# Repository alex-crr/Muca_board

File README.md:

# MUCA board v2 (MUCA2)

Readout board for printed stretchable mutual-capacitance skin sensors (reSkin / Skin-On), redesigned from the [MUCA](https://muca.cc/) board.

Status: rev 0.1, schematic complete (ERC clean), board routed (DRC 0 errors, silkscreen warnings only). Not fabricated.

## Architecture

| Block | Part | Notes |
|---|---|---|
| Touch AFE | FocalTech FT5316DME (QFN-48) | 21 TX x 12 RX = 252 nodes, I2C 0x38, <= 400 kHz. Same controller family as the original MUCA. |
| Host | Seeed Studio XIAO ESP32S3 (SMD castellated) | USB-C, 3.3 V regulator, RESET/BOOT buttons on the module. TWAI (CAN 2.0B). |
| CAN | SN65HVD230, NUP2105L TVS | 2x JST-GH 4-pin, DroneCAN pinout (1 +5 V, 2 CANH, 3 CANL, 4 GND). Solder-jumper 120 ohm termination. |
| Power | LM66100 ideal diode CAN 5 V -> XIAO 5V pin | USB powers the board through the XIAO; CAN 5 V back-feeds through the diode. XIAO 3V3 powers the whole board; ferrite-filtered +3.3VA for the FT5316 analog supplies. Max input 5.5 V. |
| Sensor I/O | 2x 2.54 mm right-angle female socket, 1x10 | J3: TX1-TX10, J4: RX1-RX10 (10 x 10), pin 1 at the right end. Sensor tails carry Amphenol Clincher 66226 pin connectors (e.g. 66226-037LF, 5 pos) on pins 1-5. |
| Debug | 7 LEDs, 7 test points | LEDs, labelled on silkscreen: CAN PWR, 3V3, TOUCH PWR (FT5316 analog rail), and the status row FAULT / COMM / SENSE / HEARTBEAT (left to right). Test points on +5V, +3V3, GND and the I2C/INT/RST bus. |

## Layout

70 x 50 mm, 2 layers. Sensing side (sensor sockets + FT5316) on the top edge, digital side (XIAO, CAN, power) on the bottom. TX/RX fans are hand-routed on F.Cu, non-crossing, over a solid B.Cu GND plane (no-tracks keepout under the sensing zone). Only the 4-wire I2C/INT/RST bus crosses between the two halves. The remaining nets were routed with a grid router: signals 0.2 mm, +3V3/+3.3VA/CAN_VBUS 0.3 mm, +5V 0.4 mm. The I2C bus needs 6 vias because J7's pin order is the reverse of U6's. Every GND pad reaches the B.Cu pour through a via.

## XIAO pin map

| XIAO pin | GPIO | Function |
|---|---|---|
| D0 / D1 | GPIO1 / GPIO2 | CAN_TX / CAN_RX |
| D2 | GPIO3 | TP_SCL |
| D3 | GPIO4 | TP_SDA |
| D4 | GPIO5 | TP_INT |
| D5 | GPIO6 | TP_RST (active low, 10 kohm pull-up) |
| D6-D9 | GPIO43, 44, 7, 8 | LED HB / SENSE / COMM / FAULT |
| D10 | GPIO9 | free |

I2C is not on the XIAO default pins: use `Wire.begin(4, 3)` (SDA, SCL). D6/D7 are UART0, so the HB/SENSE LEDs flicker with boot logs on reset.

## Files

- `MUCA2.kicad_pro` - project (hierarchical: Power, MCU, Touch AFE, CAN)
- `MUCA2.kicad_sym` - project symbols (FT5316DME from the FocalTech FT5x16 datasheet, XIAO ESP32S3 from the Seeed library)
- `MUCA2.pretty/` - project footprints (XIAO ESP32S3 SMD)

## Open points

- FT5316DME ships blank: flash `MuCaFirmware.bin` over I2C from the ESP32 ([muca-firmware](https://github.com/muca-board/muca-firmware)).
- FT5316DME sourcing not confirmed.
- Verify socket and JST-GH opening direction in the 3D viewer.
- H2 sits at (166.5, 123), 11 mm below H1, to leave room for the RX1 trace to J4 pin 1: the mounting pattern is not a rectangle.
- Silkscreen cleanup (overlapping references), no mounting holes yet.
- CAN bus power limited to 5 V nominal; a 12-24 V bus needs a buck converter.

Related: [Muca_lib](https://github.com/muca-board/Muca), [Muca_experiences](https://github.com/alex-crr/Muca_experiences).

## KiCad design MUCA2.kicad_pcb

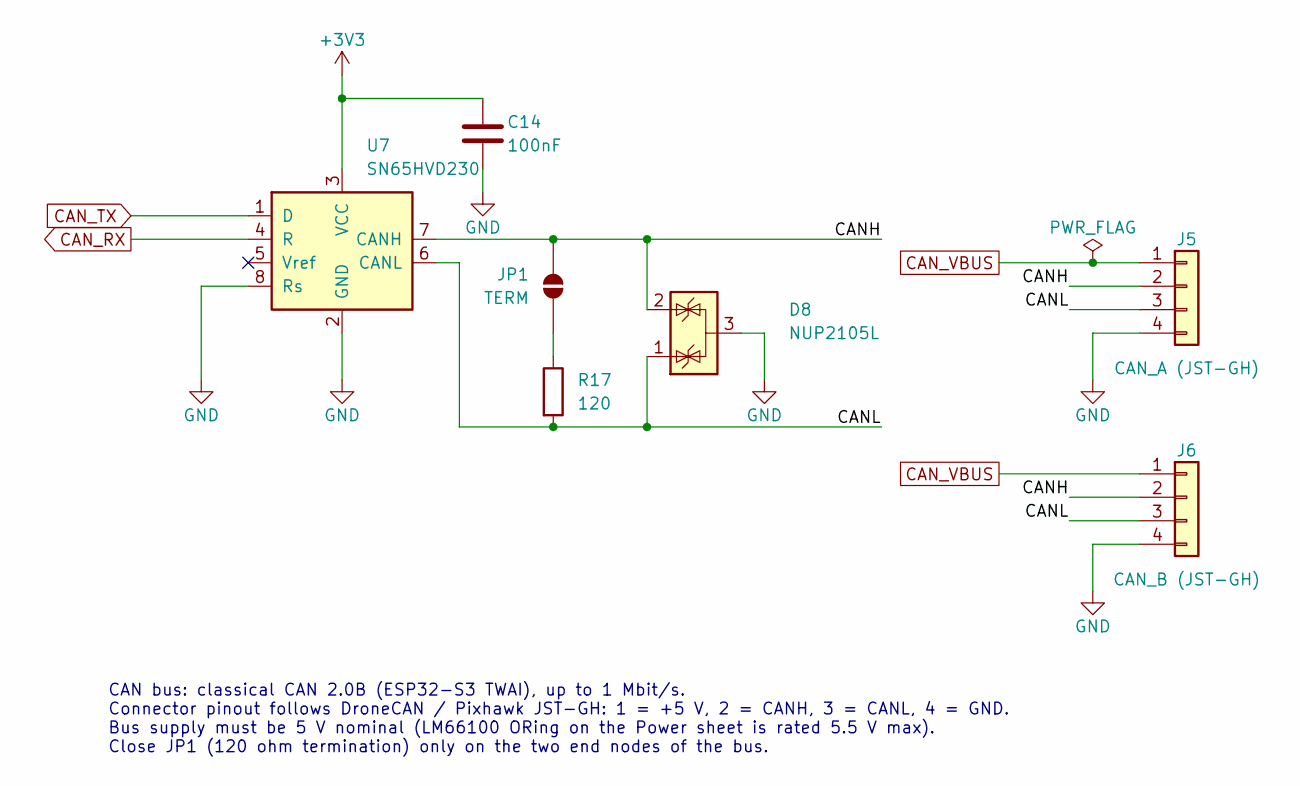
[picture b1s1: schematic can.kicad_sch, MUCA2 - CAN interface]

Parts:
C14: 100nF; C_0402_1005Metric
D8: NUP2105L; SOT-23
J5: CAN_A (JST-GH); JST_GH_SM04B-GHS-TB_1x04-1MP_P1.25mm_Horizontal
J6: CAN_B (JST-GH); JST_GH_SM04B-GHS-TB_1x04-1MP_P1.25mm_Horizontal
JP1: TERM; SolderJumper-2_P1.3mm_Open_RoundedPad1.0x1.5mm
R17: 120; R_0603_1608Metric
U7: SN65HVD230; SOIC-8_3.9x4.9mm_P1.27mm

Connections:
+3V3: C14.1, U7.3 (VCC); also elsewhere on the board
CANH: D8.2 (K), J5.2, J6.2, JP1.2 (B), U7.7 (CANH)
CANL: D8.1 (K), J5.3, J6.3, R17.2, U7.6 (CANL)
CAN_RX: U7.4 (R); also elsewhere on the board
CAN_TX: U7.1 (D); also elsewhere on the board
CAN_VBUS: J5.1, J6.1; also elsewhere on the board
GND: C14.2, D8.3 (A), J5.4, J6.4, U7.2 (GND), U7.8 (Rs); also elsewhere on the board
unnamed: JP1.1 (A), R17.1

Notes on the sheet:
CAN bus: classical CAN 2.0B (ESP32-S3 TWAI), up to 1 Mbit/s. Connector pinout follows DroneCAN / Pixhawk JST-GH: 1 = +5 V, 2 = CANH, 3 = CANL, 4 = GND. Bus supply must be 5 V nominal (LM66100 ORing on the Power sheet is rated 5.5 V max). Close JP1 (120 ohm termination) only on the two end nodes of 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

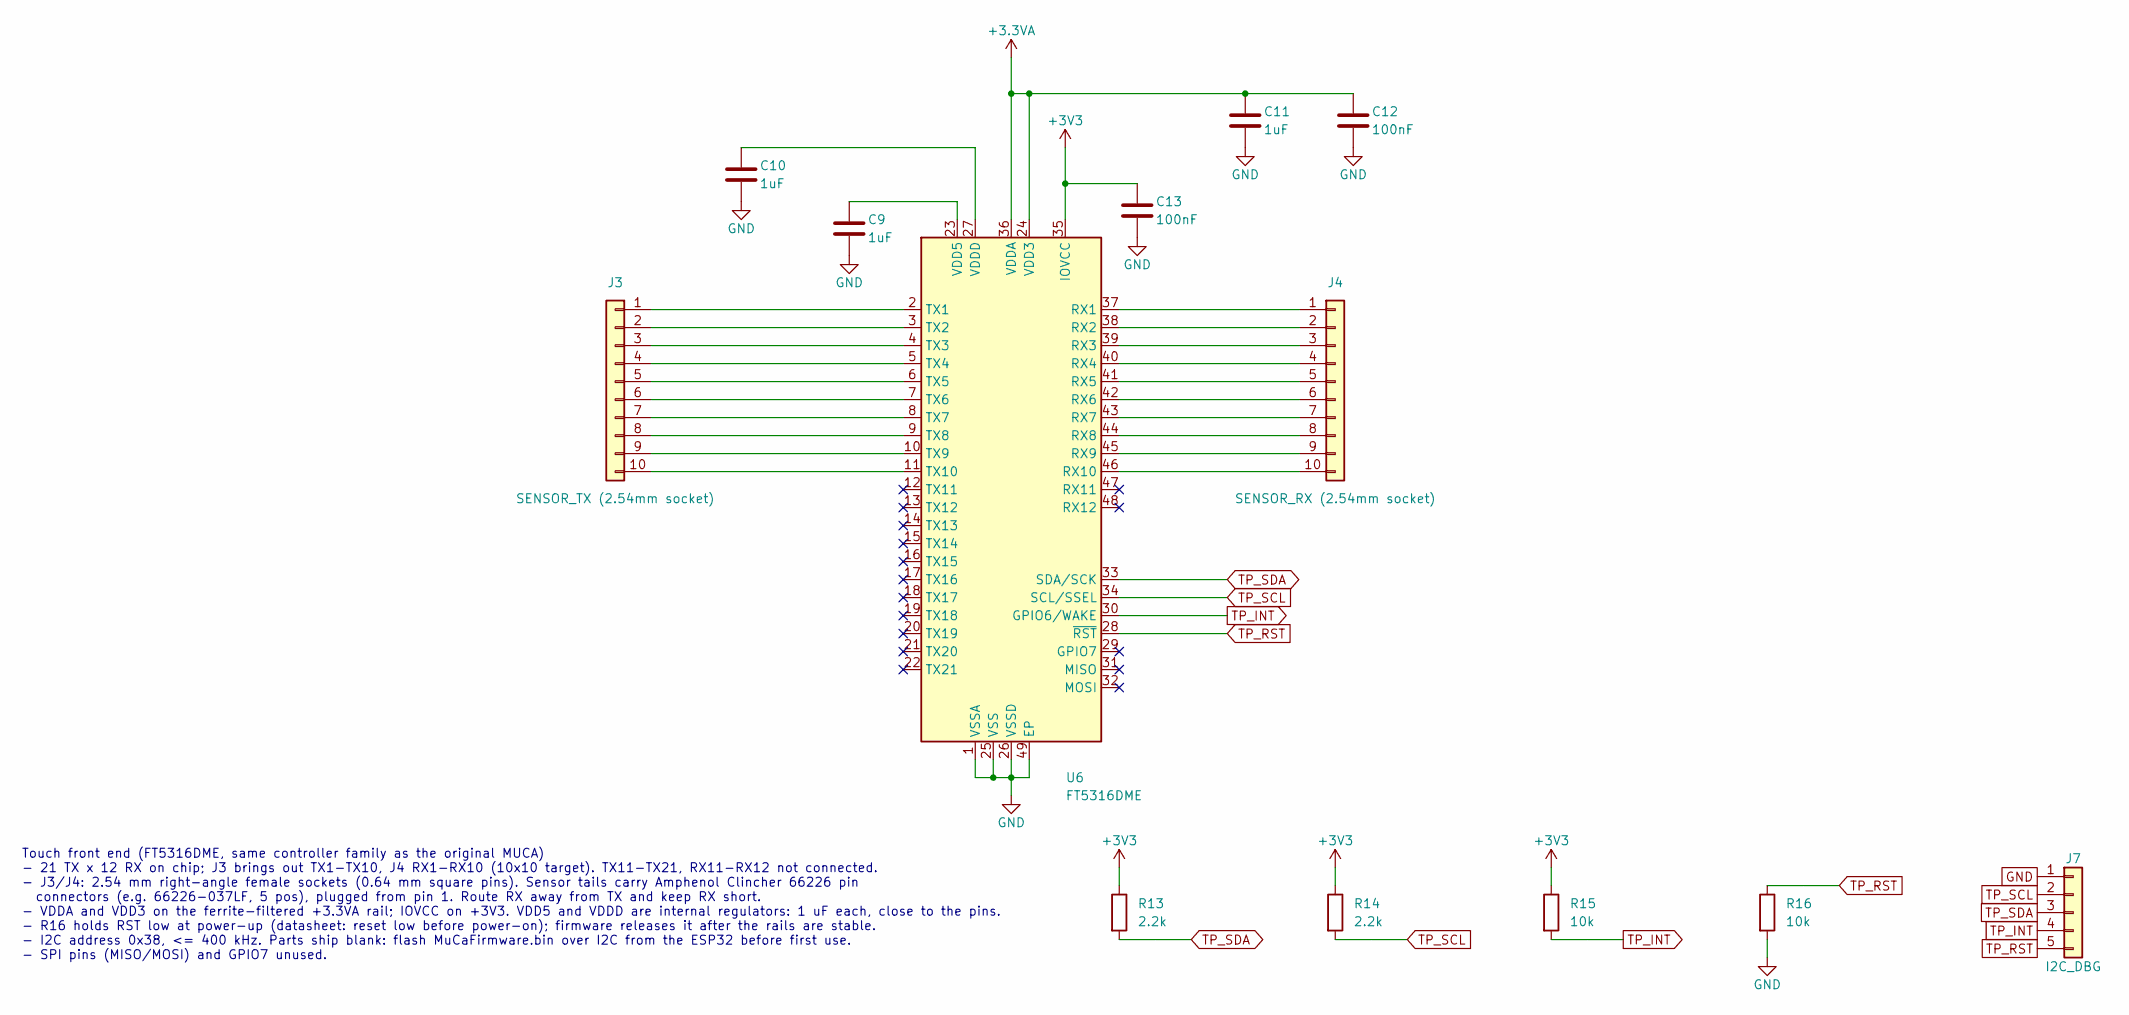
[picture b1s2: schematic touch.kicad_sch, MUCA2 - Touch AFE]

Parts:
C9, C10, C11: 1uF; C_0402_1005Metric
C12, C13: 100nF; C_0402_1005Metric
J3: SENSOR_TX (2.54mm socket); PinSocket_1x10_P2.54mm_Horizontal
J4: SENSOR_RX (2.54mm socket); PinSocket_1x10_P2.54mm_Horizontal
J7: I2C_DBG; PinHeader_1x05_P2.54mm_Vertical
R13, R14: 2.2k; R_0402_1005Metric
R15, R16: 10k; R_0402_1005Metric
U6: FT5316DME; QFN-48-1EP_6x6mm_P0.4mm_EP4.6x4.6mm

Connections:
+3.3VA: C11.1, C12.1, U6.24 (VDD3), U6.36 (VDDA); also elsewhere on the board
+3V3: C13.1, R13.1, R14.1, R15.1, U6.35 (IOVCC); also elsewhere on the board
GND: C9.2, C10.2, C11.2, C12.2, C13.2, J7.1, R16.2, U6.1 (VSSA), U6.25 (VSS), U6.26 (VSSD), U6.49 (EP); also elsewhere on the board
unnamed: C9.1, U6.23 (VDD5)
unnamed: C10.1, U6.27 (VDDD)
unnamed: J3.1, U6.2 (TX1)
unnamed: J3.2, U6.3 (TX2)
unnamed: J3.3, U6.4 (TX3)
unnamed: J3.4, U6.5 (TX4)
unnamed: J3.5, U6.6 (TX5)
unnamed: J3.6, U6.7 (TX6)
unnamed: J3.7, U6.8 (TX7)
unnamed: J3.8, U6.9 (TX8)
unnamed: J3.9, U6.10 (TX9)
unnamed: J3.10, U6.11 (TX10)
unnamed: J4.1, U6.37 (RX1)
unnamed: J4.2, U6.38 (RX2)
unnamed: J4.3, U6.39 (RX3)
unnamed: J4.4, U6.40 (RX4)
unnamed: J4.5, U6.41 (RX5)
unnamed: J4.6, U6.42 (RX6)
unnamed: J4.7, U6.43 (RX7)
unnamed: J4.8, U6.44 (RX8)
unnamed: J4.9, U6.45 (RX9)
unnamed: J4.10, U6.46 (RX10)
TP_INT: J7.4, R15.2, U6.30 (GPIO6/WAKE); also elsewhere on the board
TP_RST: J7.5, R16.1, U6.28 (~RST); also elsewhere on the board
TP_SCL: J7.2, R14.2, U6.34 (SCL/SSEL); also elsewhere on the board
TP_SDA: J7.3, R13.2, U6.33 (SDA/SCK); also elsewhere on the board

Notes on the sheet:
Touch front end (FT5316DME, same controller family as the original MUCA) - 21 TX x 12 RX on chip; J3 brings out TX1-TX10, J4 RX1-RX10 (10x10 target). TX11-TX21, RX11-RX12 not connected. - J3/J4: 2.54 mm right-angle female sockets (0.64 mm square pins). Sensor tails carry Amphenol Clincher 66226 pin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

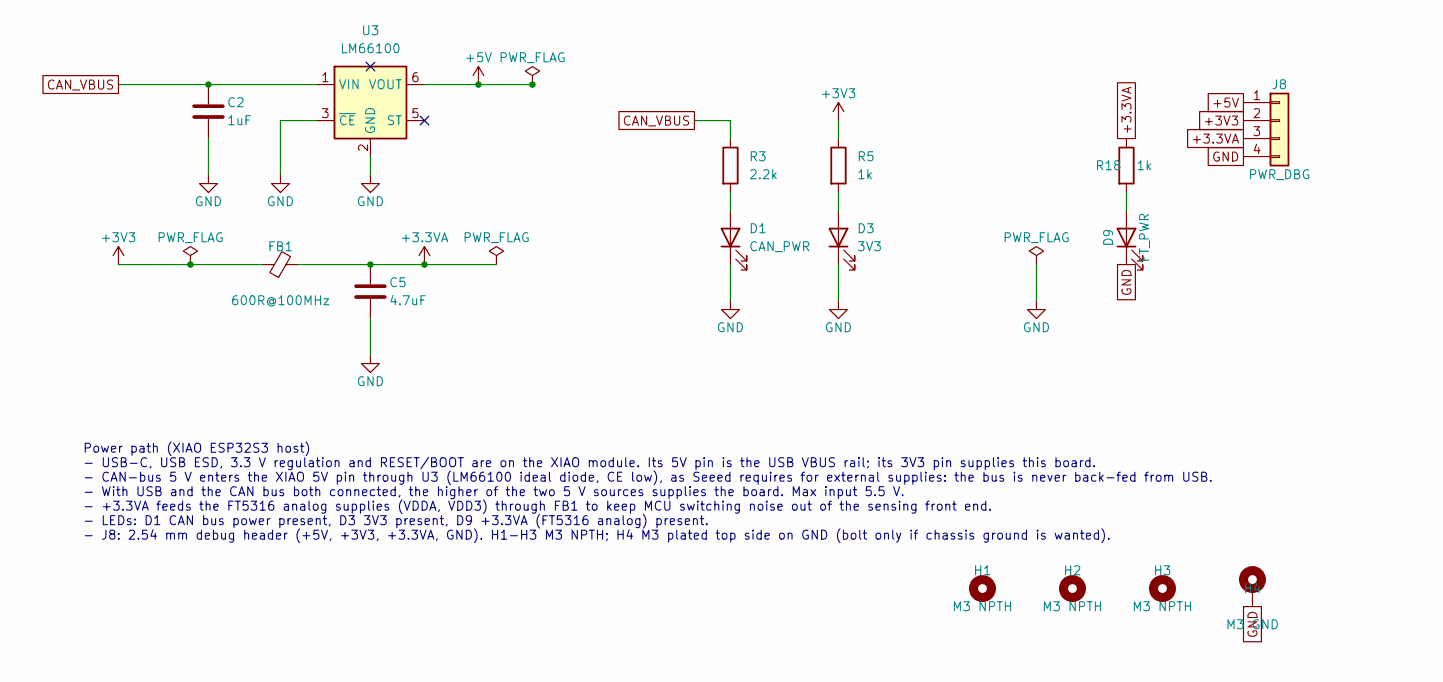
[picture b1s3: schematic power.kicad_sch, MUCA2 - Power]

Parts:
C2: 1uF; C_0402_1005Metric
C5: 4.7uF; C_0603_1608Metric
D1: CAN_PWR; LED_0603_1608Metric
D3: 3V3; LED_0603_1608Metric
D9: FT_PWR; LED_0603_1608Metric
FB1: 600R@100MHz; L_0603_1608Metric
H1, H2, H3: M3 NPTH; MountingHole_3.2mm_M3
H4: M3 GND; MountingHole_3.2mm_M3_Pad_TopOnly
J8: PWR_DBG; PinHeader_1x04_P2.54mm_Vertical
R3: 2.2k; R_0402_1005Metric
R5, R18: 1k; R_0402_1005Metric
U3: LM66100; SOT-363_SC-70-6

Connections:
+3.3VA: C5.1, FB1.2, J8.3, R18.1; also elsewhere on the board
+3V3: FB1.1, J8.2, R5.1; also elsewhere on the board
+5V: J8.1, U3.6 (VOUT); also elsewhere on the board
CAN_VBUS: C2.1, R3.1, U3.1 (VIN); also elsewhere on the board
GND: C2.2, C5.2, D1.1 (K), D3.1 (K), D9.1 (K), H4.1, J8.4, U3.2 (GND), U3.3 (~CE); also elsewhere on the board
unnamed: D1.2 (A), R3.2
unnamed: D3.2 (A), R5.2
unnamed: D9.2 (A), R18.2

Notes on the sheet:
Power path (XIAO ESP32S3 host) - USB-C, USB ESD, 3.3 V regulation and RESET/BOOT are on the XIAO module. Its 5V pin is the USB VBUS rail; its 3V3 pin supplies this board. - CAN-bus 5 V enters the XIAO 5V pin through U3 (LM66100 ideal diode, CE low), as Seeed requires for external supplies: the bus 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

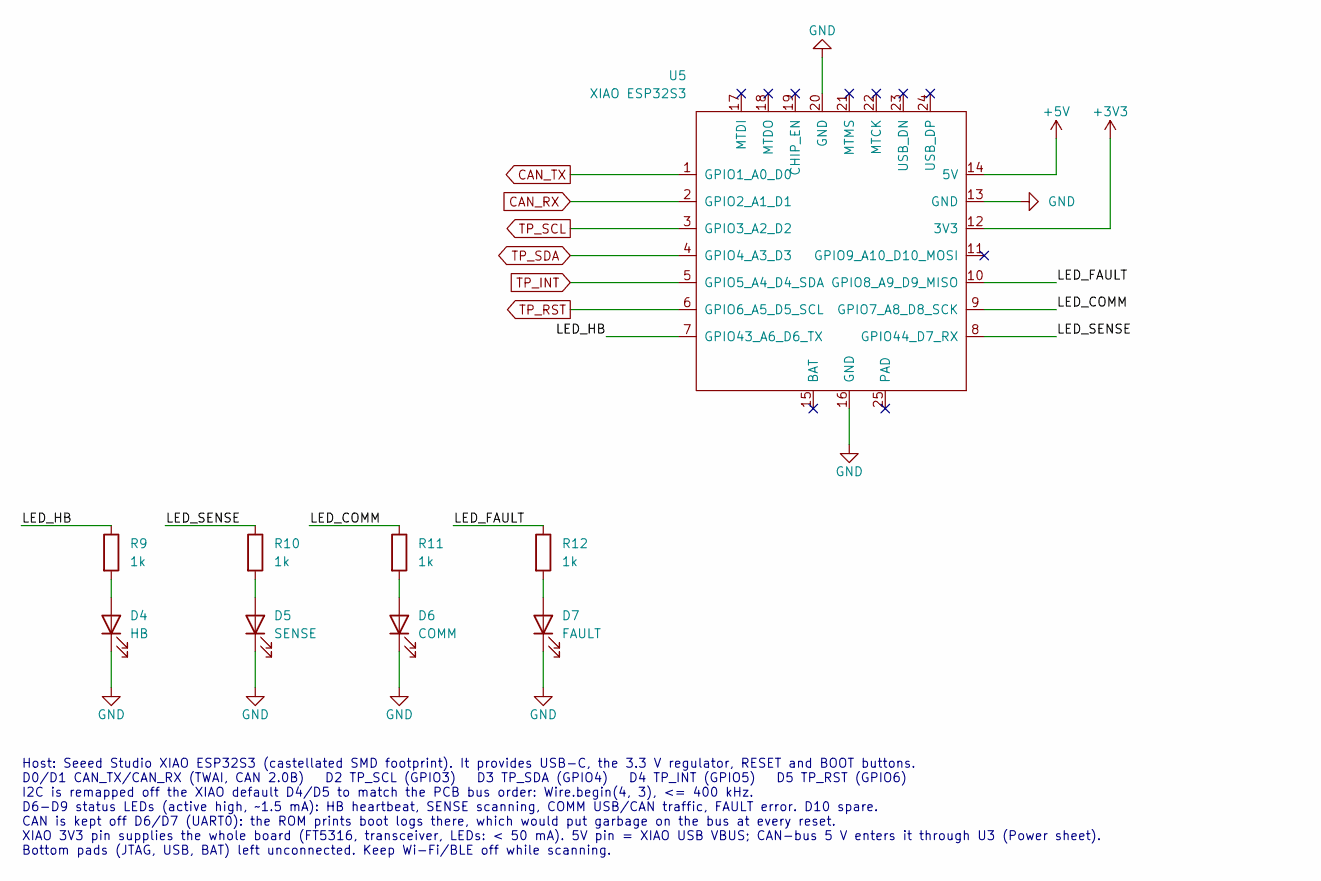
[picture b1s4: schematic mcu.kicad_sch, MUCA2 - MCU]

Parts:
D4: HB; LED_0603_1608Metric
D5: SENSE; LED_0603_1608Metric
D6: COMM; LED_0603_1608Metric
D7: FAULT; LED_0603_1608Metric
R9, R10, R11, R12: 1k; R_0402_1005Metric
U5: XIAO ESP32S3; XIAO-ESP32S3-SMD

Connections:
+3V3: U5.12 (3V3); also elsewhere on the board
+5V: U5.14 (5V); also elsewhere on the board
CAN_RX: U5.2 (GPIO2_A1_D1); also elsewhere on the board
CAN_TX: U5.1 (GPIO1_A0_D0); also elsewhere on the board
GND: D4.1 (K), D5.1 (K), D6.1 (K), D7.1 (K), U5.13 (GND), U5.16 (GND), U5.20 (GND); also elsewhere on the board
LED_COMM: R11.1, U5.9 (GPIO7_A8_D8_SCK)
LED_FAULT: R12.1, U5.10 (GPIO8_A9_D9_MISO)
LED_HB: R9.1, U5.7 (GPIO43_A6_D6_TX)
LED_SENSE: R10.1, U5.8 (GPIO44_D7_RX)
unnamed: D4.2 (A), R9.2
unnamed: D5.2 (A), R10.2
unnamed: D6.2 (A), R11.2
unnamed: D7.2 (A), R12.2
TP_INT: U5.5 (GPIO5_A4_D4_SDA); also elsewhere on the board
TP_RST: U5.6 (GPIO6_A5_D5_SCL); also elsewhere on the board
TP_SCL: U5.3 (GPIO3_A2_D2); also elsewhere on the board
TP_SDA: U5.4 (GPIO4_A3_D3); also elsewhere on the board

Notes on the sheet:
Host: Seeed Studio XIAO ESP32S3 (castellated SMD footprint). It provides USB-C, the 3.3 V regulator, RESET and BOOT buttons. D0/D1 CAN_TX/CAN_RX (TWAI, CAN 2.0B) D2 TP_SCL (GPIO3) D3 TP_SDA (GPIO4) D4 TP_INT (GPIO5) D5 TP_RST (GPIO6) I2C is remapped off the XIAO default D4/D5 to match the PCB bus o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

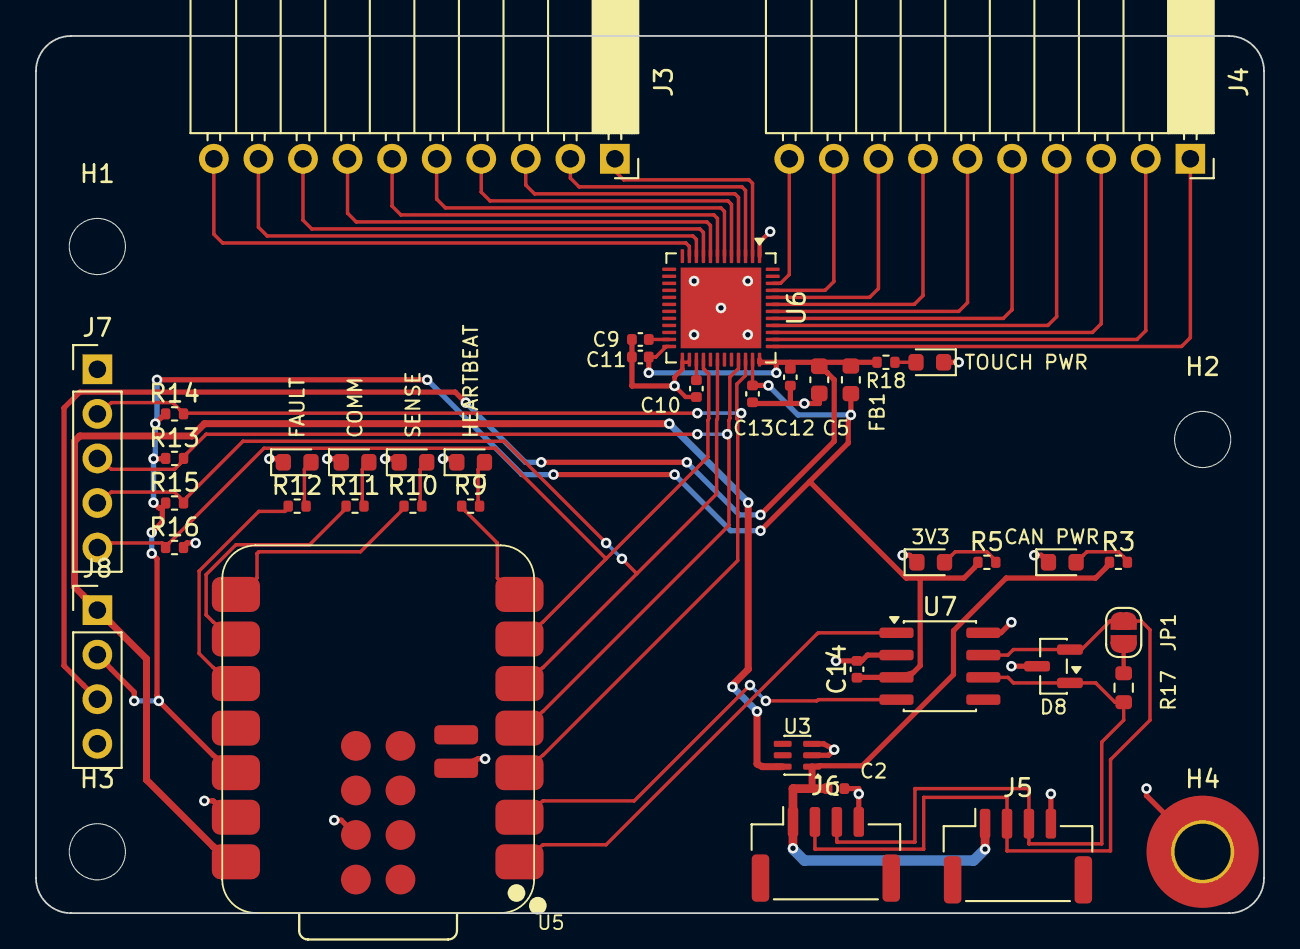
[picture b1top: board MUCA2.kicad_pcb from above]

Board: 2 copper layers, 70.0 x 50.0 mm, 44 parts (0 on the bottom side), 47 nets.

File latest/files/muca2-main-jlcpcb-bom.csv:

Comment,Designator,Footprint,LCSC Part #
1uF,"C2,C9,C10,C11",C_0402_1005Metric,
4.7uF,C5,C_0603_1608Metric,
100nF,"C12,C13,C14",C_0402_1005Metric,
CAN_PWR,D1,LED_0603_1608Metric,
3V3,D3,LED_0603_1608Metric,
HB,D4,LED_0603_1608Metric,
SENSE,D5,LED_0603_1608Metric,
COMM,D6,LED_0603_1608Metric,
FAULT,D7,LED_0603_1608Metric,
NUP2105L,D8,SOT-23,
FT_PWR,D9,LED_0603_1608Metric,
600R@100MHz,FB1,L_0603_1608Metric,
SENSOR_TX (2.54mm socket),J3,PinSocket_1x10_P2.54mm_Horizontal,
SENSOR_RX (2.54mm socket),J4,PinSocket_1x10_P2.54mm_Horizontal,
CAN_A (JST-GH),J5,JST_GH_SM04B-GHS-TB_1x04-1MP_P1.25mm_Horizontal,
CAN_B (JST-GH),J6,JST_GH_SM04B-GHS-TB_1x04-1MP_P1.25mm_Horizontal,
I2C_DBG,J7,PinHeader_1x05_P2.54mm_Vertical,
PWR_DBG,J8,PinHeader_1x04_P2.54mm_Vertical,
2.2k,"R3,R13,R14",R_0402_1005Metric,
1k,"R5,R9,R10,R11,R12,R18",R_0402_1005Metric,
10k,"R15,R16",R_0402_1005Metric,
120,R17,R_0603_1608Metric,
LM66100,U3,SOT-363_SC-70-6,
XIAO ESP32S3,U5,XIAO-ESP32S3-SMD,
FT5316DME,U6,QFN-48-1EP_6x6mm_P0.4mm_EP4.6x4.6mm,
SN65HVD230,U7,SOIC-8_3.9x4.9mm_P1.27mm,
